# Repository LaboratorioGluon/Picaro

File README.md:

# Picaro project

The picaro project is a HAB Picoballoon developed from scratch live on Twitch/Youtube.

## Objectives

- Float at around 13km height.
- Report sensor data to ground using LoRa.
- Last at least a couple of days alive.

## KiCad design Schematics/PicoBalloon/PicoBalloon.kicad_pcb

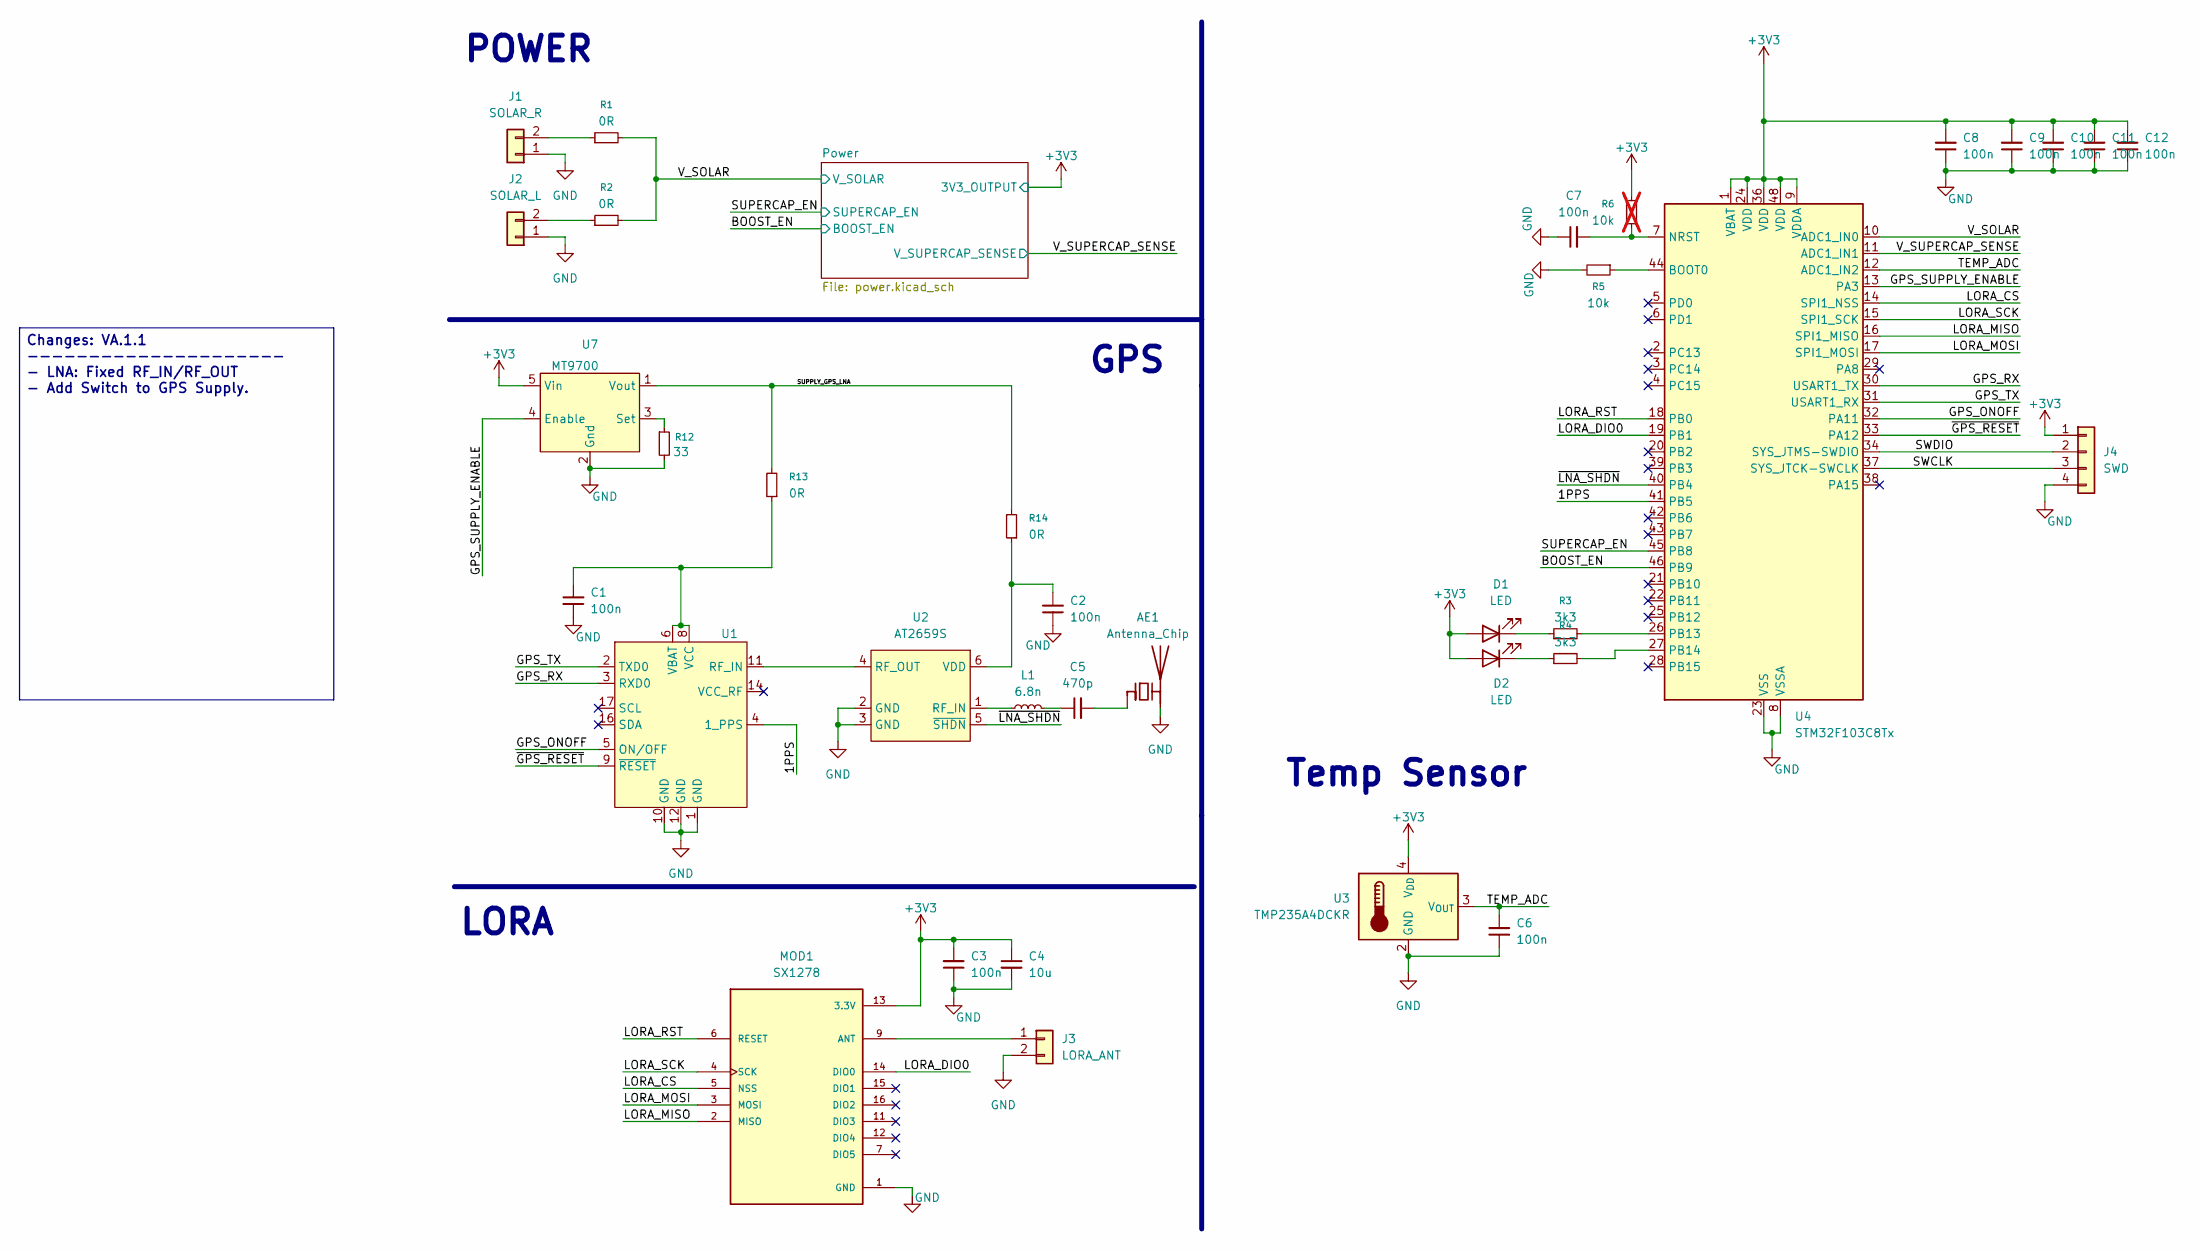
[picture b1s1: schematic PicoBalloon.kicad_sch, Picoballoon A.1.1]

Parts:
AE1: Antenna_Chip; Pulse_W3011
C1, C2, C3, C6, C7, C8, C9, C10, C11, C12: 100n; C_0603_1608Metric_Pad1.08x0.95mm_HandSolder
C4: 10u; C_0805_2012Metric_Pad1.18x1.45mm_HandSolder
C5: 470p; C_0603_1608Metric_Pad1.08x0.95mm_HandSolder
D1, D2: LED; LED_0603_1608Metric_Pad1.05x0.95mm_HandSolder
J1: SOLAR_R; 2_PAD_SMD
J2: SOLAR_L; 2_PAD_SMD
J3: LORA_ANT; PinHeader_1x02_P2.00mm_Vertical
J4: SWD; PinHeader_1x04_P2.54mm_Vertical
L1: 6.8n; L_0603_1608Metric_Pad1.05x0.95mm_HandSolder
MOD1: SX1278; PARTREV N/A
R1, R2, R13, R14: 0R; R_0603_1608Metric_Pad0.98x0.95mm_HandSolder
R3, R4: 3k3; R_0603_1608Metric_Pad0.98x0.95mm_HandSolder
R5: 10k; R_0603_1608Metric_Pad0.98x0.95mm_HandSolder
R6: 10k; R_0603_1608Metric_Pad0.98x0.95mm_HandSolder; not fitted
R12: 33; R_0603_1608Metric_Pad0.98x0.95mm_HandSolder
U1: ATGM336H
U2: AT2659S; SOT-23-6_Handsoldering
U3: TMP235A4DCKR; SOT-353_SC-70-5
U4: STM32F103C8Tx; LQFP-48_7x7mm_P0.5mm
U7: MT9700; SOT-23-5_HandSoldering

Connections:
+3V3: C3.2, C4.1, C8.2, C9.2, C10.2, C11.2, C12.2, D1.2 (A), D2.2 (A), J4.1, MOD1.13 (3.3V), R6.1, U3.4 (V_{DD}), U4.1 (VBAT), U4.9 (VDDA), U4.24 (VDD), U4.36 (VDD), U4.48 (VDD), U7.5 (Vin); also elsewhere on the board
/1PPS: U1.4 (1_PPS), U4.41 (PB5)
/BOOST_EN: U4.46 (PB9); also elsewhere on the board
/GPS_ONOFF: U1.5 (ON/OFF), U4.32 (PA11)
/GPS_RX: U1.3 (RXD0), U4.30 (USART1_TX)
/GPS_SUPPLY_ENABLE: U4.13 (PA3), U7.4 (Enable)
/GPS_TX: U1.2 (TXD0), U4.31 (USART1_RX)
/LORA_CS: MOD1.5 (NSS), U4.14 (SPI1_NSS)
/LORA_DIO0: MOD1.14 (DIO0), U4.19 (PB1)
/LORA_MISO: MOD1.2 (MISO), U4.16 (SPI1_MISO)
/LORA_MOSI: MOD1.3 (MOSI), U4.17 (SPI1_MOSI)
/LORA_RST: MOD1.6 (RESET), U4.18 (PB0)
/LORA_SCK: MOD1.4 (SCK), U4.15 (SPI1_SCK)
/SUPERCAP_EN: U4.45 (PB8); also elsewhere on the board
/SUPPLY_GPS_LNA: R13.2, R14.2, U7.1 (Vout)
/SWCLK: J4.3, U4.37 (SYS_JTCK-SWCLK)
/SWDIO: J4.2, U4.34 (SYS_JTMS-SWDIO)
/TEMP_ADC: C6.2, U3.3 (V_{OUT}), U4.12 (ADC1_IN2)
/V_SOLAR: R1.2, R2.2, U4.10 (ADC1_IN0); also elsewhere on the board
/V_SUPERCAP_SENSE: U4.11 (ADC1_IN1); also elsewhere on the board
/~GPS_RESET: U1.9 (~RESET), U4.33 (PA12)
/~LNA_SHDN: U2.5 (~SHDN), U4.40 (PB4)
GND: AE1.2 (PCB_Trace), C1.1, C2.1, C3.1, C4.2, C6.1, C7.1, C8.1, C9.1, C10.1, C11.1, C12.1, J1.1, J2.1, J3.2, J4.4, MOD1.1 (GND), MOD1.8 (GND), MOD1.10 (GND), R5.2, R12.2, U1.1 (GND), U1.10 (GND), U1.12 (GND), U2.2 (GND), U2.3 (GND), U3.2 (GND), U3.5 (GND), U4.8 (VSSA), U4.23 (VSS), U4.35 (VSS), U4.47 (VSS), U7.2 (Gnd); also elsewhere on the board
unnamed: AE1.1 (FEED), C5.2
unnamed: C5.1, L1.2
unnamed: D1.1 (K), R3.1
unnamed: D2.1 (K), R4.1
unnamed: J1.2, R1.1
unnamed: J2.2, R2.1
unnamed: J3.1, MOD1.9 (ANT)
unnamed: U1.11 (RF_IN), U2.4 (RF_OUT)
unnamed: C1.2, R13.1, U1.6 (VBAT), U1.8 (VCC)
unnamed: L1.1, U2.1 (RF_IN)
unnamed: C2.2, R14.1, U2.6 (VDD)
unnamed: R5.1, U4.44 (BOOT0)
unnamed: C7.2, R6.2, U4.7 (NRST)
unnamed: R3.2, U4.26 (PB13)
unnamed: R4.2, U4.27 (PB14)
unnamed: R12.1, U7.3 (Set)

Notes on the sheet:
Temp Sensor
POWER
LORA
GPS
Changes: VA.1.1 --------------------- - LNA: Fixed RF_IN/RF_OUT - Add Switch to GPS Supply.

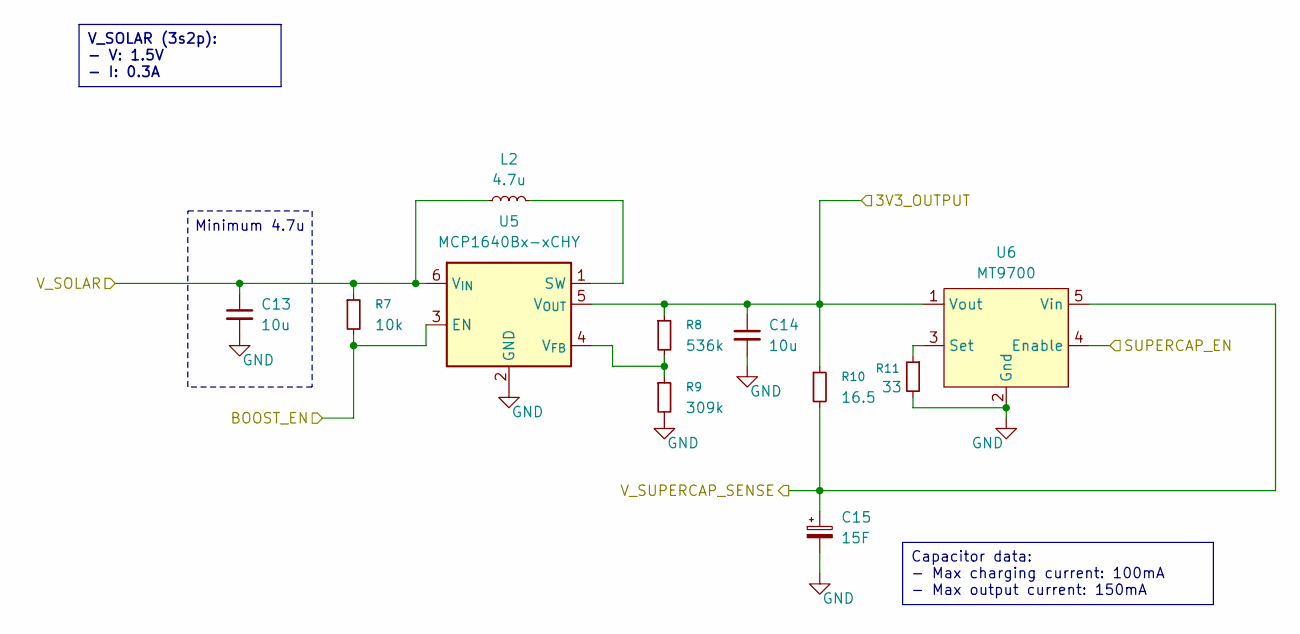
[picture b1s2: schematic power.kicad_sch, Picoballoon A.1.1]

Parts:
C13, C14: 10u; C_0805_2012Metric_Pad1.18x1.45mm_HandSolder
C15: 15F; CP_EIA-3528-12_Kemet-T_HandSolder
L2: 4.7u; L_1008_2520Metric_Pad1.43x2.20mm_HandSolder
R7: 10k; R_0603_1608Metric_Pad0.98x0.95mm_HandSolder
R8: 536k; R_0603_1608Metric_Pad0.98x0.95mm_HandSolder
R9: 309k; R_0603_1608Metric_Pad0.98x0.95mm_HandSolder
R10: 16.5; R_2010_5025Metric_Pad1.40x2.65mm_HandSolder
R11: 33; R_0603_1608Metric_Pad0.98x0.95mm_HandSolder
U5: MCP1640Bx-xCHY; SOT-23-6
U6: MT9700; SOT-23-5_HandSoldering

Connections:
+3V3: C14.1, R8.1, R10.1, U5.5 (V_{OUT}), U6.1 (Vout); also elsewhere on the board
/BOOST_EN: R7.2, U5.3 (EN); also elsewhere on the board
/SUPERCAP_EN: U6.4 (Enable); also elsewhere on the board
/V_SOLAR: C13.1, L2.1, R7.1, U5.6 (V_{IN}); also elsewhere on the board
/V_SUPERCAP_SENSE: C15.1, R10.2, U6.5 (Vin); also elsewhere on the board
GND: C13.2, C14.2, C15.2, R9.2, R11.2, U5.2 (GND), U6.2 (Gnd); also elsewhere on the board
unnamed: L2.2, U5.1 (SW)
unnamed: R8.2, R9.1, U5.4 (V_{FB})
unnamed: R11.1, U6.3 (Set)

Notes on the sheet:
Minimum 4.7u
V_SOLAR (3s2p): - V: 1.5V - I: 0.3A
Capacitor data: - Max charging current: 100mA - Max output current: 150mA

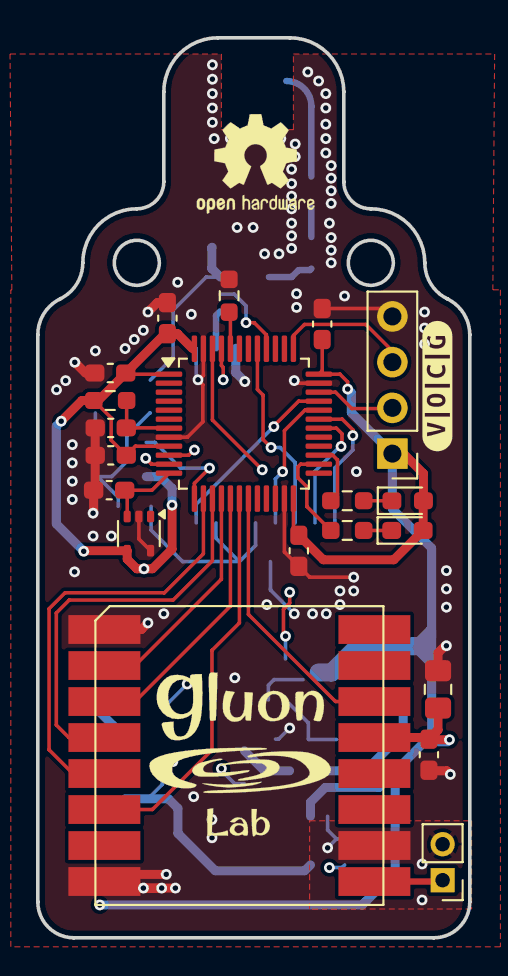
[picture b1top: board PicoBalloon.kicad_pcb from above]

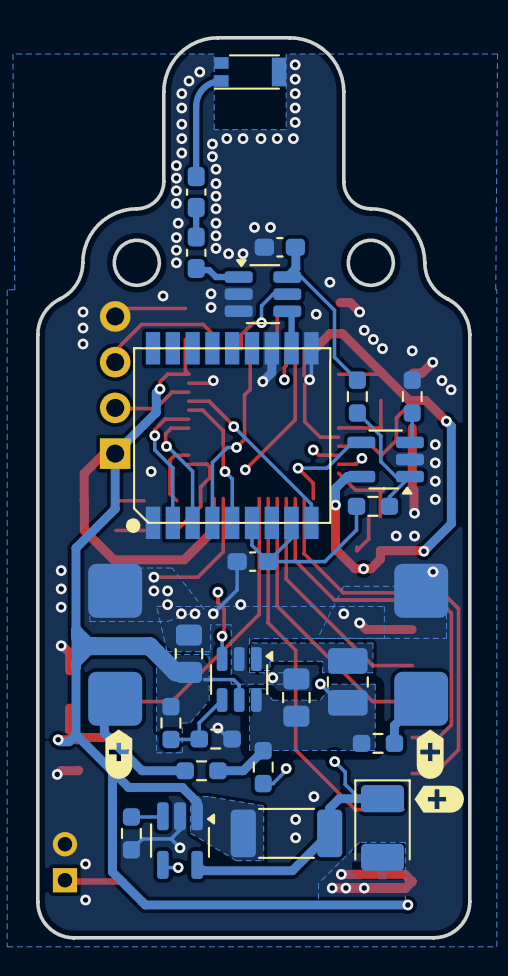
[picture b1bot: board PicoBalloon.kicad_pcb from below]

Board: 4 copper layers, 24.0 x 50.0 mm, 50 parts (29 on the bottom side), 42 nets.

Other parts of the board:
kibuzzard-68A4CDDF: G***; kibuzzard-68A4CDDF
kibuzzard-688BBDB2, kibuzzard-688BBDB2#2, kibuzzard-688BBDB2#3: G***; kibuzzard-688BBDB2

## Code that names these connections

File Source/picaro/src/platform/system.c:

#include "platform/system.h"
#include "pinout.h"
#include <stm32f1xx_hal.h>
#include <string.h>

typedef struct {
    GPIO_TypeDef*    port;
    GPIO_InitTypeDef gpioDef;
} gpioInitConfig;

/*************************/
/** GPIO CONFIGURATION  **/
/*************************/

const gpioInitConfig gpioConfig[] = {

    // ADC
    { ADC_VSOLAR_PORT,      { ADC_VSOLAR_PIN, GPIO_MODE_ANALOG, GPIO_NOPULL, GPIO_SPEED_FREQ_LOW }         },
    { ADC_VCAP_PORT,        { ADC_VCAP_PIN, GPIO_MODE_ANALOG, GPIO_NOPULL, GPIO_SPEED_FREQ_LOW }           },
    { ADC_TEMP_PORT,        { ADC_TEMP_PIN, GPIO_MODE_ANALOG, GPIO_NOPULL, GPIO_SPEED_FREQ_LOW }           },

    // GPS - UART
    { GPS_RX_PORT,          { GPS_RX_PIN, GPIO_MODE_AF_PP, GPIO_NOPULL, GPIO_SPEED_FREQ_LOW }              },
    { GPS_TX_PORT,          { GPS_TX_PIN, GPIO_MODE_AF_INPUT, GPIO_NOPULL, GPIO_SPEED_FREQ_LOW }           },
    { GPS_NRESET_PORT,      { GPS_NRESET_PIN, GPIO_MODE_OUTPUT_PP, GPIO_NOPULL, GPIO_SPEED_FREQ_LOW }      }, // GPS_RESET
    { GPS_LNASHDN_PORT,     { GPS_LNASHDN_PIN, GPIO_MODE_OUTPUT_PP, GPIO_NOPULL, GPIO_SPEED_FREQ_LOW }     }, // LNA_SHDN
    { GPS_ONOFF_PORT,       { GPS_ONOFF_PIN, GPIO_MODE_OUTPUT_PP, GPIO_NOPULL, GPIO_SPEED_FREQ_LOW }       },
    // GPS_ONOFF

    /*{ GPS_RX_PORT,          { GPS_RX_PIN, GPIO_MODE_ANALOG, GPIO_NOPULL, GPIO_SPEED_FREQ_LOW }             },
    { GPS_TX_PORT,          { GPS_TX_PIN, GPIO_MODE_ANALOG, GPIO_NOPULL, GPIO_SPEED_FREQ_LOW }             },
    { GPS_NRESET_PORT,      { GPS_NRESET_PIN, GPIO_MODE_ANALOG, GPIO_NOPULL, GPIO_SPEED_FREQ_LOW }         }, // GPS_RESET
    { GPS_LNASHDN_PORT,     { GPS_LNASHDN_PIN, GPIO_MODE_ANALOG, GPIO_NOPULL, GPIO_SPEED_FREQ_LOW }        }, // LNA_SHDN
    { GPS_ONOFF_PORT,       { GPS_ONOFF_PIN, GPIO_MODE_ANALOG, GPIO_NOPULL, GPIO_SPEED_FREQ_LOW }          },*/
    // GPS_ONOFF

    // DEBUG - UART
    { GPIOB,                { GPIO_PIN_10, GPIO_MODE_AF_PP, GPIO_NOPULL, GPIO_SPEED_FREQ_LOW }             },
    { GPIOB,                { GPIO_PIN_11, GPIO_MODE_AF_INPUT, GPIO_NOPULL, GPIO_SPEED_FREQ_LOW }          },

    // LEDS - GPIO
    { LEDS_RED_PORT,        { LEDS_RED_PIN, GPIO_MODE_OUTPUT_PP, GPIO_NOPULL, GPIO_SPEED_FREQ_LOW }        },

    // PSU
    { PSU_SUPERCAP_EN_PORT, { PSU_SUPERCAP_EN_PIN, GPIO_MODE_OUTPUT_PP, GPIO_NOPULL, GPIO_SPEED_FREQ_LOW } }, // SUPERCAP_EN
    { PSU_BOOST_EN_PORT,    { PSU_BOOST_EN_PIN, GPIO_MODE_OUTPUT_PP, GPIO_NOPULL, GPIO_SPEED_FREQ_LOW }    }  // BOOST_EN
};

const uint32_t gpioConfigSize = sizeof(gpioConfig) / sizeof(gpioInitConfig);

/************************************************/

static void system_initAllGpio()
{
    /* GPIO Ports Clock Enable */
    __HAL_RCC_GPIOA_CLK_ENABLE();
    __HAL_RCC_GPIOB_CLK_ENABLE();
    __HAL_RCC_GPIOC_CLK_ENABLE();
    __HAL_RCC_GPIOD_CLK_ENABLE();

    GPIO_InitTypeDef config;
    config.Mode  = GPIO_MODE_INPUT;
    config.Pin   = GPIO_PIN_All;
    config.Pull  = GPIO_PULLDOWN;
    config.Speed = GPIO_SPEED_FREQ_LOW;
    // HAL_GPIO_Init(gpioConfig[i].port, &gpioConfig[i].gpioDef);
    HAL_GPIO_Init(GPIOA, &config);
    HAL_GPIO_Init(GPIOB, &config);
    HAL_GPIO_Init(GPIOC, &config);
    HAL_GPIO_Init(GPIOD, &config);

    HAL_GPIO_WritePin(GPIOA, GPIO_PIN_All, GPIO_PIN_RESET);
    HAL_GPIO_WritePin(GPIOB, GPIO_PIN_All, GPIO_PIN_RESET);
    HAL_GPIO_WritePin(GPIOC, GPIO_PIN_All, GPIO_PIN_RESET);
    HAL_GPIO_WritePin(GPIOD, GPIO_PIN_All, GPIO_PIN_RESET);

    __HAL_RCC_GPIOA_CLK_DISABLE();
    __HAL_RCC_GPIOB_CLK_DISABLE();
    __HAL_RCC_GPIOC_CLK_DISABLE();
    __HAL_RCC_GPIOD_CLK_DISABLE();
}

static void system_initGpio()
{
    system_initAllGpio();

    __HAL_RCC_GPIOA_CLK_ENABLE();
    __HAL_RCC_GPIOB_CLK_ENABLE();
    __HAL_RCC_GPIOC_CLK_ENABLE();
    __HAL_RCC_GPIOD_CLK_ENABLE();

    for (uint32_t i = 0; i < gpioConfigSize; i++) {
        HAL_GPIO_Init(gpioConfig[i].port, &gpioConfig[i].gpioDef);
    }

    HAL_GPIO_WritePin(PSU_BOOST_EN_PORT, PSU_BOOST_EN_PIN, GPIO_PIN_RESET);

    __HAL_RCC_GPIOA_CLK_DISABLE();
    __HAL_RCC_GPIOB_CLK_DISABLE();
    __HAL_RCC_GPIOC_CLK_DISABLE();
    __HAL_RCC_GPIOD_CLK_DISABLE();
    /*HAL_GPIO_WritePin(GPS_ONOFF_PORT, GPS_ONOFF_PIN, GPIO_PIN_RESET);
    HAL_GPIO_WritePin(GPS_NRESET_PORT, GPS_NRESET_PIN, GPIO_PIN_RESET);
    HAL_GPIO_WritePin(GPS_LNASHDN_PORT, GPS_LNASHDN_PIN, GPIO_PIN_RESET);

    HAL_GPIO_WritePin(PSU_SUPERCAP_EN_PORT, PSU_SUPERCAP_EN_PIN, GPIO_PIN_RESET);
    HAL_GPIO_WritePin(PSU_BOOST_EN_PORT, PSU_BOOST_EN_PIN, GPIO_PIN_RESET);*/
}

static void system_initClocks()
{
    RCC_OscInitTypeDef       RCC_OscInitStruct = { 0 };
    RCC_ClkInitTypeDef       RCC_ClkInitStruct = { 0 };
    RCC_PeriphCLKInitTypeDef PeriphClkInit     = { 0 };

    /** Initializes the RCC Oscillators according to the specified parameters
     * in the RCC_OscInitTypeDef structure.
     */
    RCC_OscInitStruct.OscillatorType      = RCC_OSCILLATORTYPE_HSI | RCC_OSCILLATORTYPE_LSI;
    RCC_OscInitStruct.HSIState            = RCC_HSI_ON;
    RCC_OscInitStruct.HSICalibrationValue = RCC_HSICALIBRATION_DEFAULT;
    RCC_OscInitStruct.LSIState            = RCC_LSI_ON;
    RCC_OscInitStruct.PLL.PLLState        = RCC_PLL_NONE;
    /*RCC_OscInitStruct.PLL.PLLState  = RCC_PLL_ON;
    RCC_OscInitStruct.PLL.PLLSource = RCC_PLLSOURCE_HSI_DIV2;
    RCC_OscInitStruct.PLL.PLLMUL    = RCC_PLL_MUL12;*/
    if (HAL_RCC_OscConfig(&RCC_OscInitStruct) != HAL_OK) {
        // Error_Handler();
    }

    /** Initializes the CPU, AHB and APB buses clocks
     */
    RCC_ClkInitStruct.ClockType = RCC_CLOCKTYPE_HCLK | RCC_CLOCKTYPE_SYSCLK | RCC_CLOCKTYPE_PCLK1 | RCC_CLOCKTYPE_PCLK2;
    // RCC_ClkInitStruct.SYSCLKSource = RCC_SYSCLKSOURCE_PLLCLK;
    RCC_ClkInitStruct.SYSCLKSource   = RCC_SYSCLKSOURCE_HSE;
    RCC_ClkInitStruct.AHBCLKDivider  = RCC_SYSCLK_DIV1;
    RCC_ClkInitStruct.APB1CLKDivider = RCC_HCLK_DIV2;
    RCC_ClkInitStruct.APB2CLKDivider = RCC_HCLK_DIV1;

    if (HAL_RCC_ClockConfig(&RCC_ClkInitStruct, FLASH_LATENCY_0) != HAL_OK) {
        // Error_Handler();
    }
    PeriphClkInit.PeriphClockSelection = RCC_PERIPHCLK_RTC | RCC_PERIPHCLK_ADC;
    PeriphClkInit.RTCClockSelection    = RCC_RTCCLKSOURCE_LSI;
    PeriphClkInit.AdcClockSelection    = RCC_ADCPCLK2_DIV4;
    if (HAL_RCCEx_PeriphCLKConfig(&PeriphClkInit) != HAL_OK) {
        // Error_Handler();
    }
}

void system_init()
{
    system_initClocks();
    system_initGpio();
}

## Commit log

2025-07-25 GPS v1, BME removed, added temp sensor
2025-07-27 Updated Schematics for the Boost
2025-07-28 Finished schematic V1
2025-07-28 Updated R10 size and datasheets
2025-07-28 Fixed footprints and schematic symbols
2025-07-29 First PCB layout
2025-07-31 Version 1.0 provisional de la PCB
2025-07-31 Cleared groups in PCB
2025-08-02 Added gerber files for v1.0
2025-08-05 Added GPS support
2025-08-11 Added CASIC library to configure GPS
2025-08-11 Added debug UART and improved GPIO initialization
2025-08-11 Added debug uart
2025-08-11 Added configuration file, and modified GPS debug
2025-08-12 Fixed EOLs
2025-08-12 Improved warnings and minor improvements in CASIC code
2025-08-20 Started working on PCB A1.1
2025-10-12 Working RTC
2025-10-12 Updated PCB
2025-10-20 Version PCB A1.1
